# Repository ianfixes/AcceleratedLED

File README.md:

# AcceleratedLED
Controls LEDs using input from Accelerometer

# Setup

## Setting up Arduino and Compiling the Code (MAC)

1. Clone this repo to `~/Documents/Arduino` with `cd ~/Documents/Arduino && git clone git@github.com:bguest/AcceleratedLED.git`
2. Change directory to AcceleratedLED with `cd AcceleratedLED`
3. Mod setup script `chmod +x setup.sh`
4. Run Setup `.\setup.sh` this will clone correct versions of `Adafruit_WS2801`
5. Download Arduino
6. Launch Arduino
7. Open AcceleratedLED328
8. Set board to `Arduino Pro or Pro Mini`
9. Set processor to `ATMega328P 5v 16MHz`
10. Verify and Upload Code

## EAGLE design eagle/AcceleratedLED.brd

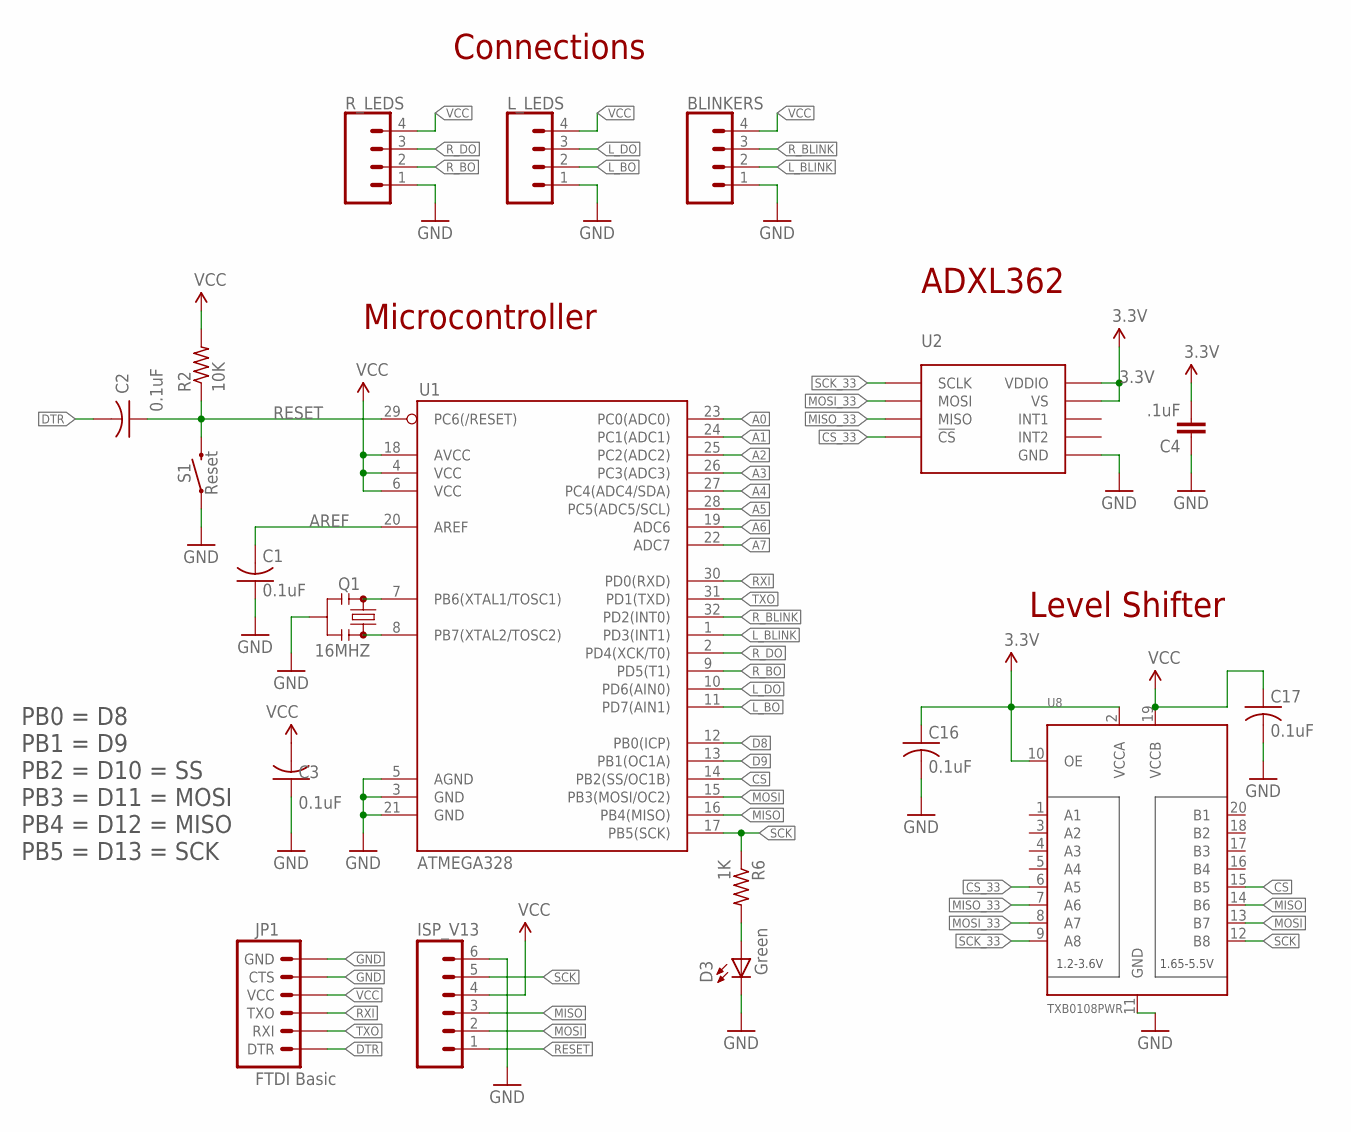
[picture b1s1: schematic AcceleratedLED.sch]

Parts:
BLINKERS: CONN_04JST-PTH; JST-4-PTH
C1, C2, C3, C16, C17: 0.1uF; C0805
C4: .1uF; 0603-CAP
D3: Green; CHIPLED_0805
ISP_V13: M06SIP; 1X06
JP1: FTDI Basic; 1X06
L_LEDS: CONN_04JST-PTH; JST-4-PTH
Q1: 16MHZ; RESONATOR-SMD
R2: 10K; M0805
R6: 1K; M0805
R_LEDS: CONN_04JST-PTH; JST-4-PTH
S1: Reset; TACTILE_SWITCH_SMD_5.2MM
U1: ATMEGA328; TQFP32-08
U2: ADXL362ADXL362-1:1; ADXL362-1:1
U8: TXB0108PWR; TSSOP20

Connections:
3.3V: C4.2, C16.1, U2.P$1 (VDDIO), U2.P$14 (VS), U8.2 (VCCA), U8.10 (OE)
A0: U1.23 (PC0(ADC0))
A1: U1.24 (PC1(ADC1))
A2: U1.25 (PC2(ADC2))
A3: U1.26 (PC3(ADC3))
A4: U1.27 (PC4(ADC4/SDA))
A5: U1.28 (PC5(ADC5/SCL))
A6: U1.19 (ADC6)
A7: U1.22 (ADC7)
AREF: C1.2, U1.20 (AREF)
CS: U1.14 (PB2(SS/OC1B)), U8.15 (B5)
CS_33: U2.P$8 (!CS), U8.6 (A5)
D8: U1.12 (PB0(ICP))
D9: U1.13 (PB1(OC1A))
DTR: C2.2, JP1.1 (DTR)
GND: BLINKERS.1, C1.1, C3.1, C4.1, C16.2, C17.2, D3.C, ISP_V13.6, JP1.5 (CTS), JP1.6 (GND), L_LEDS.1, Q1.2, R_LEDS.1, S1.1, S1.2 (1), U1.3 (GND), U1.5 (AGND), U1.21 (GND), U2.P$12 (GND), U2.P$13 (GND), U2.P$16 (GND), U8.11 (GND)
L_BLINK: BLINKERS.2, U1.1 (PD3(INT1))
L_BO: L_LEDS.2, U1.11 (PD7(AIN1))
L_DO: L_LEDS.3, U1.10 (PD6(AIN0))
MISO: ISP_V13.3, U1.16 (PB4(MISO)), U8.14 (B6)
MISO_33: U2.P$7 (MISO), U8.7 (A6)
MOSI: ISP_V13.2, U1.15 (PB3(MOSI/OC2)), U8.13 (B7)
MOSI_33: U2.P$6 (MOSI), U8.8 (A7)
unnamed: Q1.3, U1.8 (PB7(XTAL2/TOSC2))
unnamed: Q1.1, U1.7 (PB6(XTAL1/TOSC1))
unnamed: D3.A, R6.2
RESET: C2.1, ISP_V13.1, R2.1, S1.3 (2), S1.4 (2), U1.29 (PC6(/RESET))
RXI: JP1.3 (TXO), U1.30 (PD0(RXD))
R_BLINK: BLINKERS.3, U1.32 (PD2(INT0))
R_BO: R_LEDS.2, U1.9 (PD5(T1))
R_DO: R_LEDS.3, U1.2 (PD4(XCK/T0))
SCK: ISP_V13.5, R6.1, U1.17 (PB5(SCK)), U8.12 (B8)
SCK_33: U2.P$4 (SCLK), U8.9 (A8)
TXO: JP1.2 (RXI), U1.31 (PD1(TXD))
VCC: BLINKERS.4, C3.2, C17.1, ISP_V13.4, JP1.4 (VCC), L_LEDS.4, R2.2, R_LEDS.4, U1.4 (VCC), U1.6 (VCC), U1.18 (AVCC), U8.19 (VCCB)

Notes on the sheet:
Microcontroller
Level Shifter
ADXL362
Connections
PB0 = D8 PB1 = D9 PB2 = D10 = SS PB3 = D11 = MOSI PB4 = D12 = MISO PB5 = D13 = SCK

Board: 2 copper layers, 19 parts (0 on the bottom side), 25 nets, no tracks yet.

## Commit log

2018-08-09 Add Eagle Files
2018-08-10 Set pins to things
2018-08-24 Tweaks to blinker
2018-08-29 Get Acclerometer working
2018-09-10 Use Arduino 1.5 library structure
2018-09-10 fix typo
2018-09-14 Add arduino_ci unit tests

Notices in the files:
parts and their libraries:
SparkFun-Sensors: Licensing: CC v3.0 Share-Alike You are welcome to use this library for commercial purposes.
